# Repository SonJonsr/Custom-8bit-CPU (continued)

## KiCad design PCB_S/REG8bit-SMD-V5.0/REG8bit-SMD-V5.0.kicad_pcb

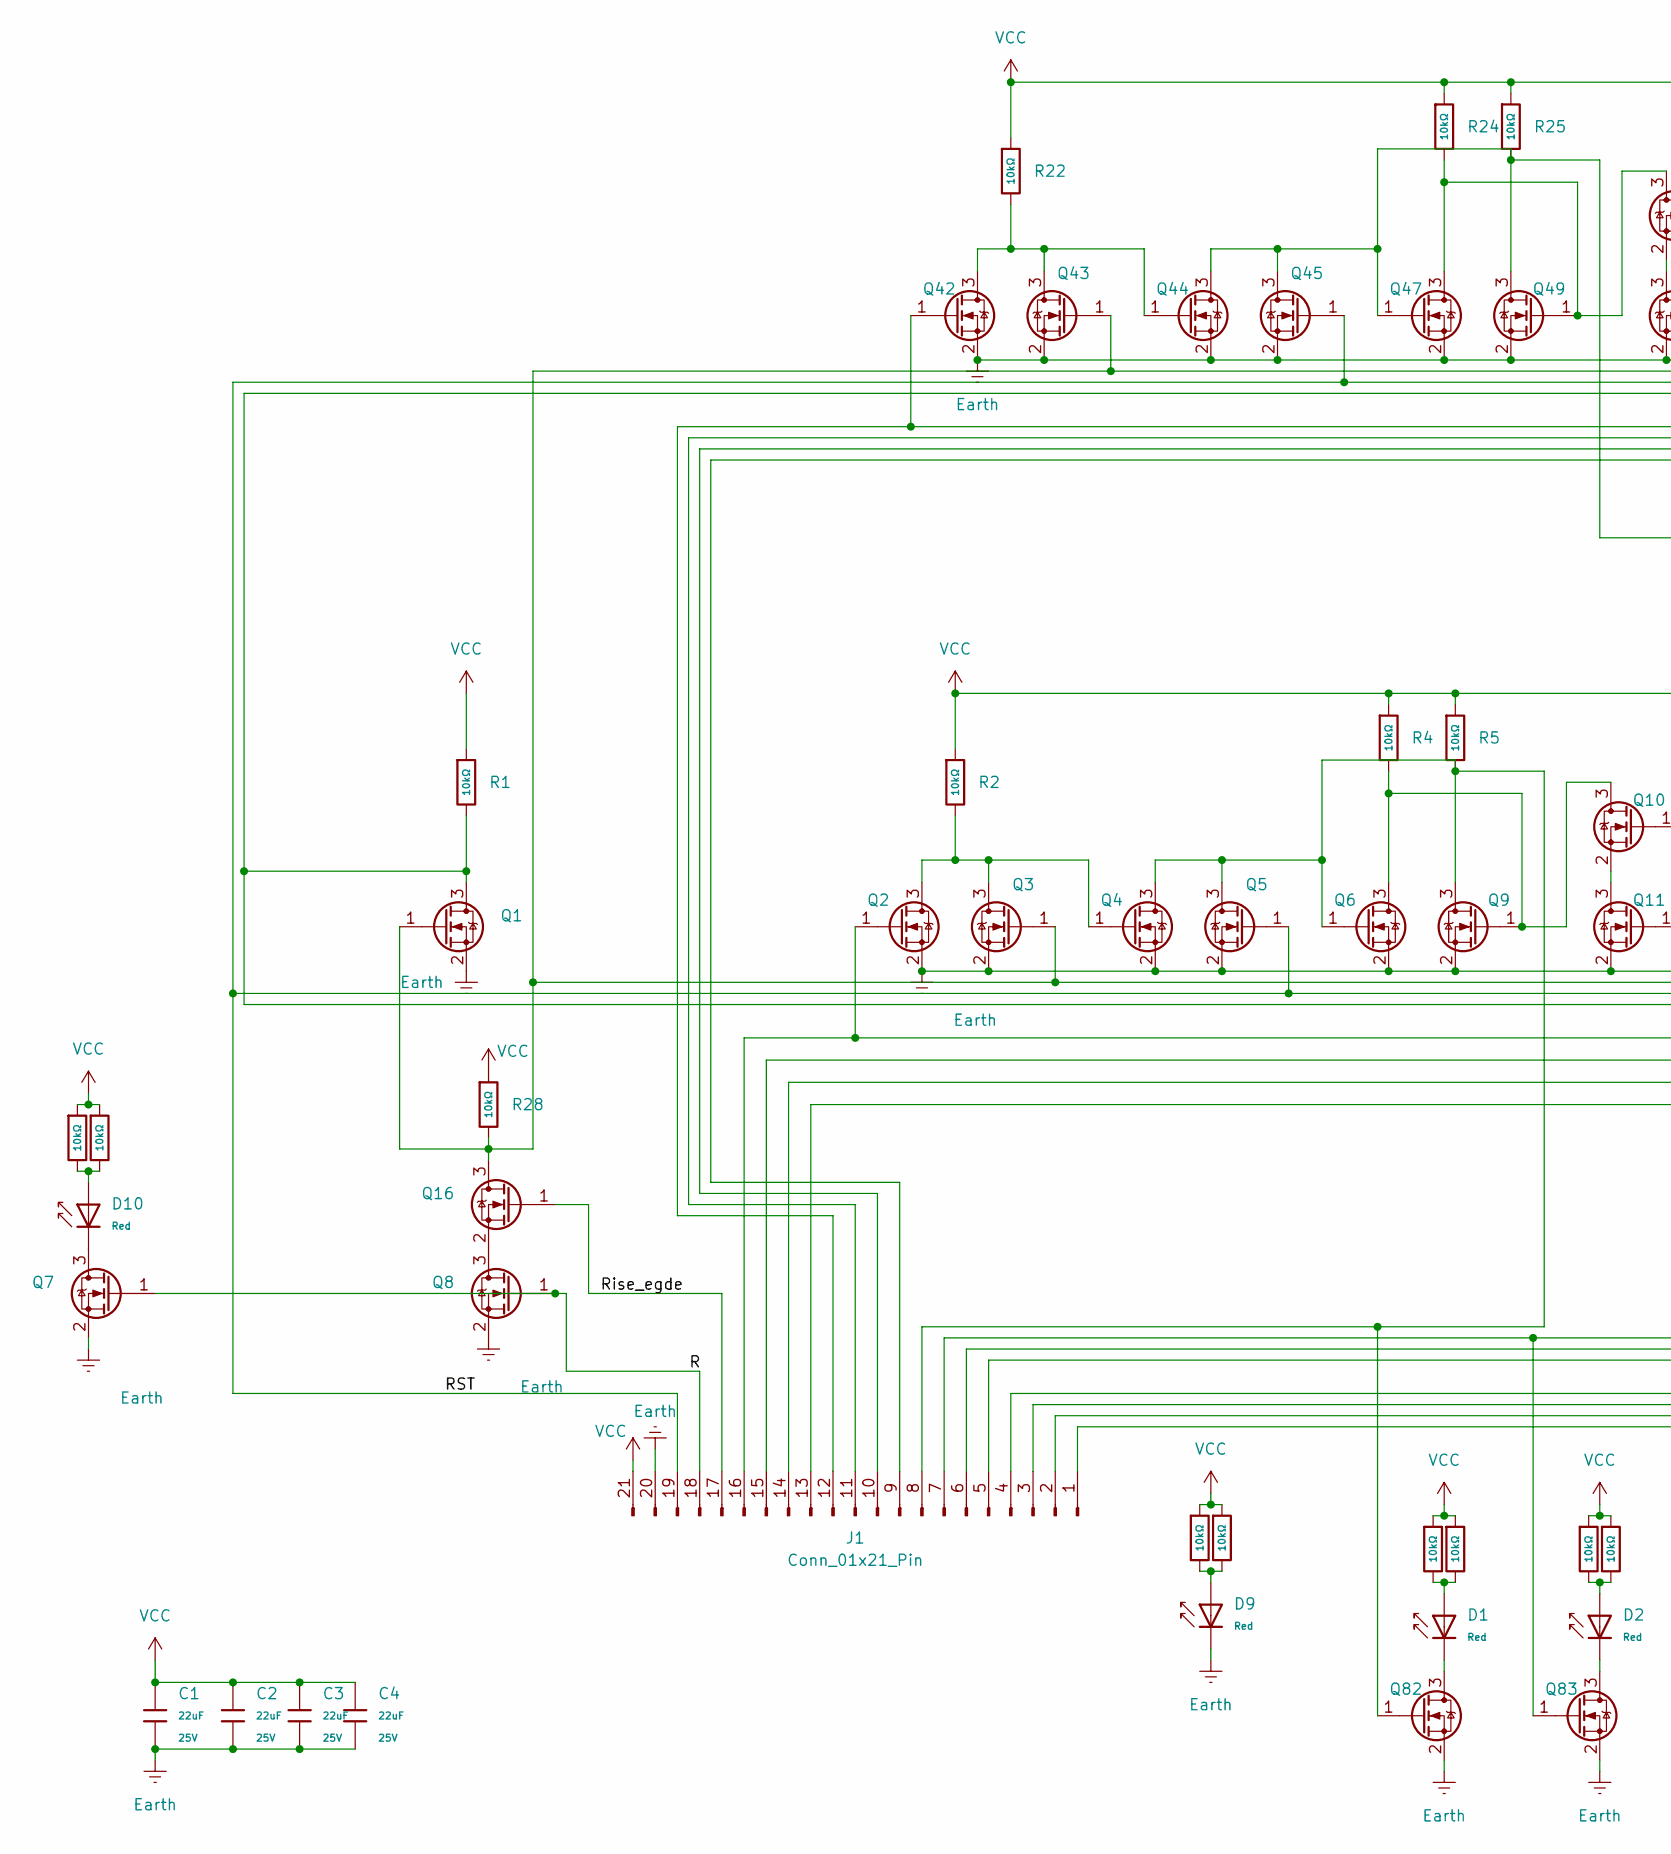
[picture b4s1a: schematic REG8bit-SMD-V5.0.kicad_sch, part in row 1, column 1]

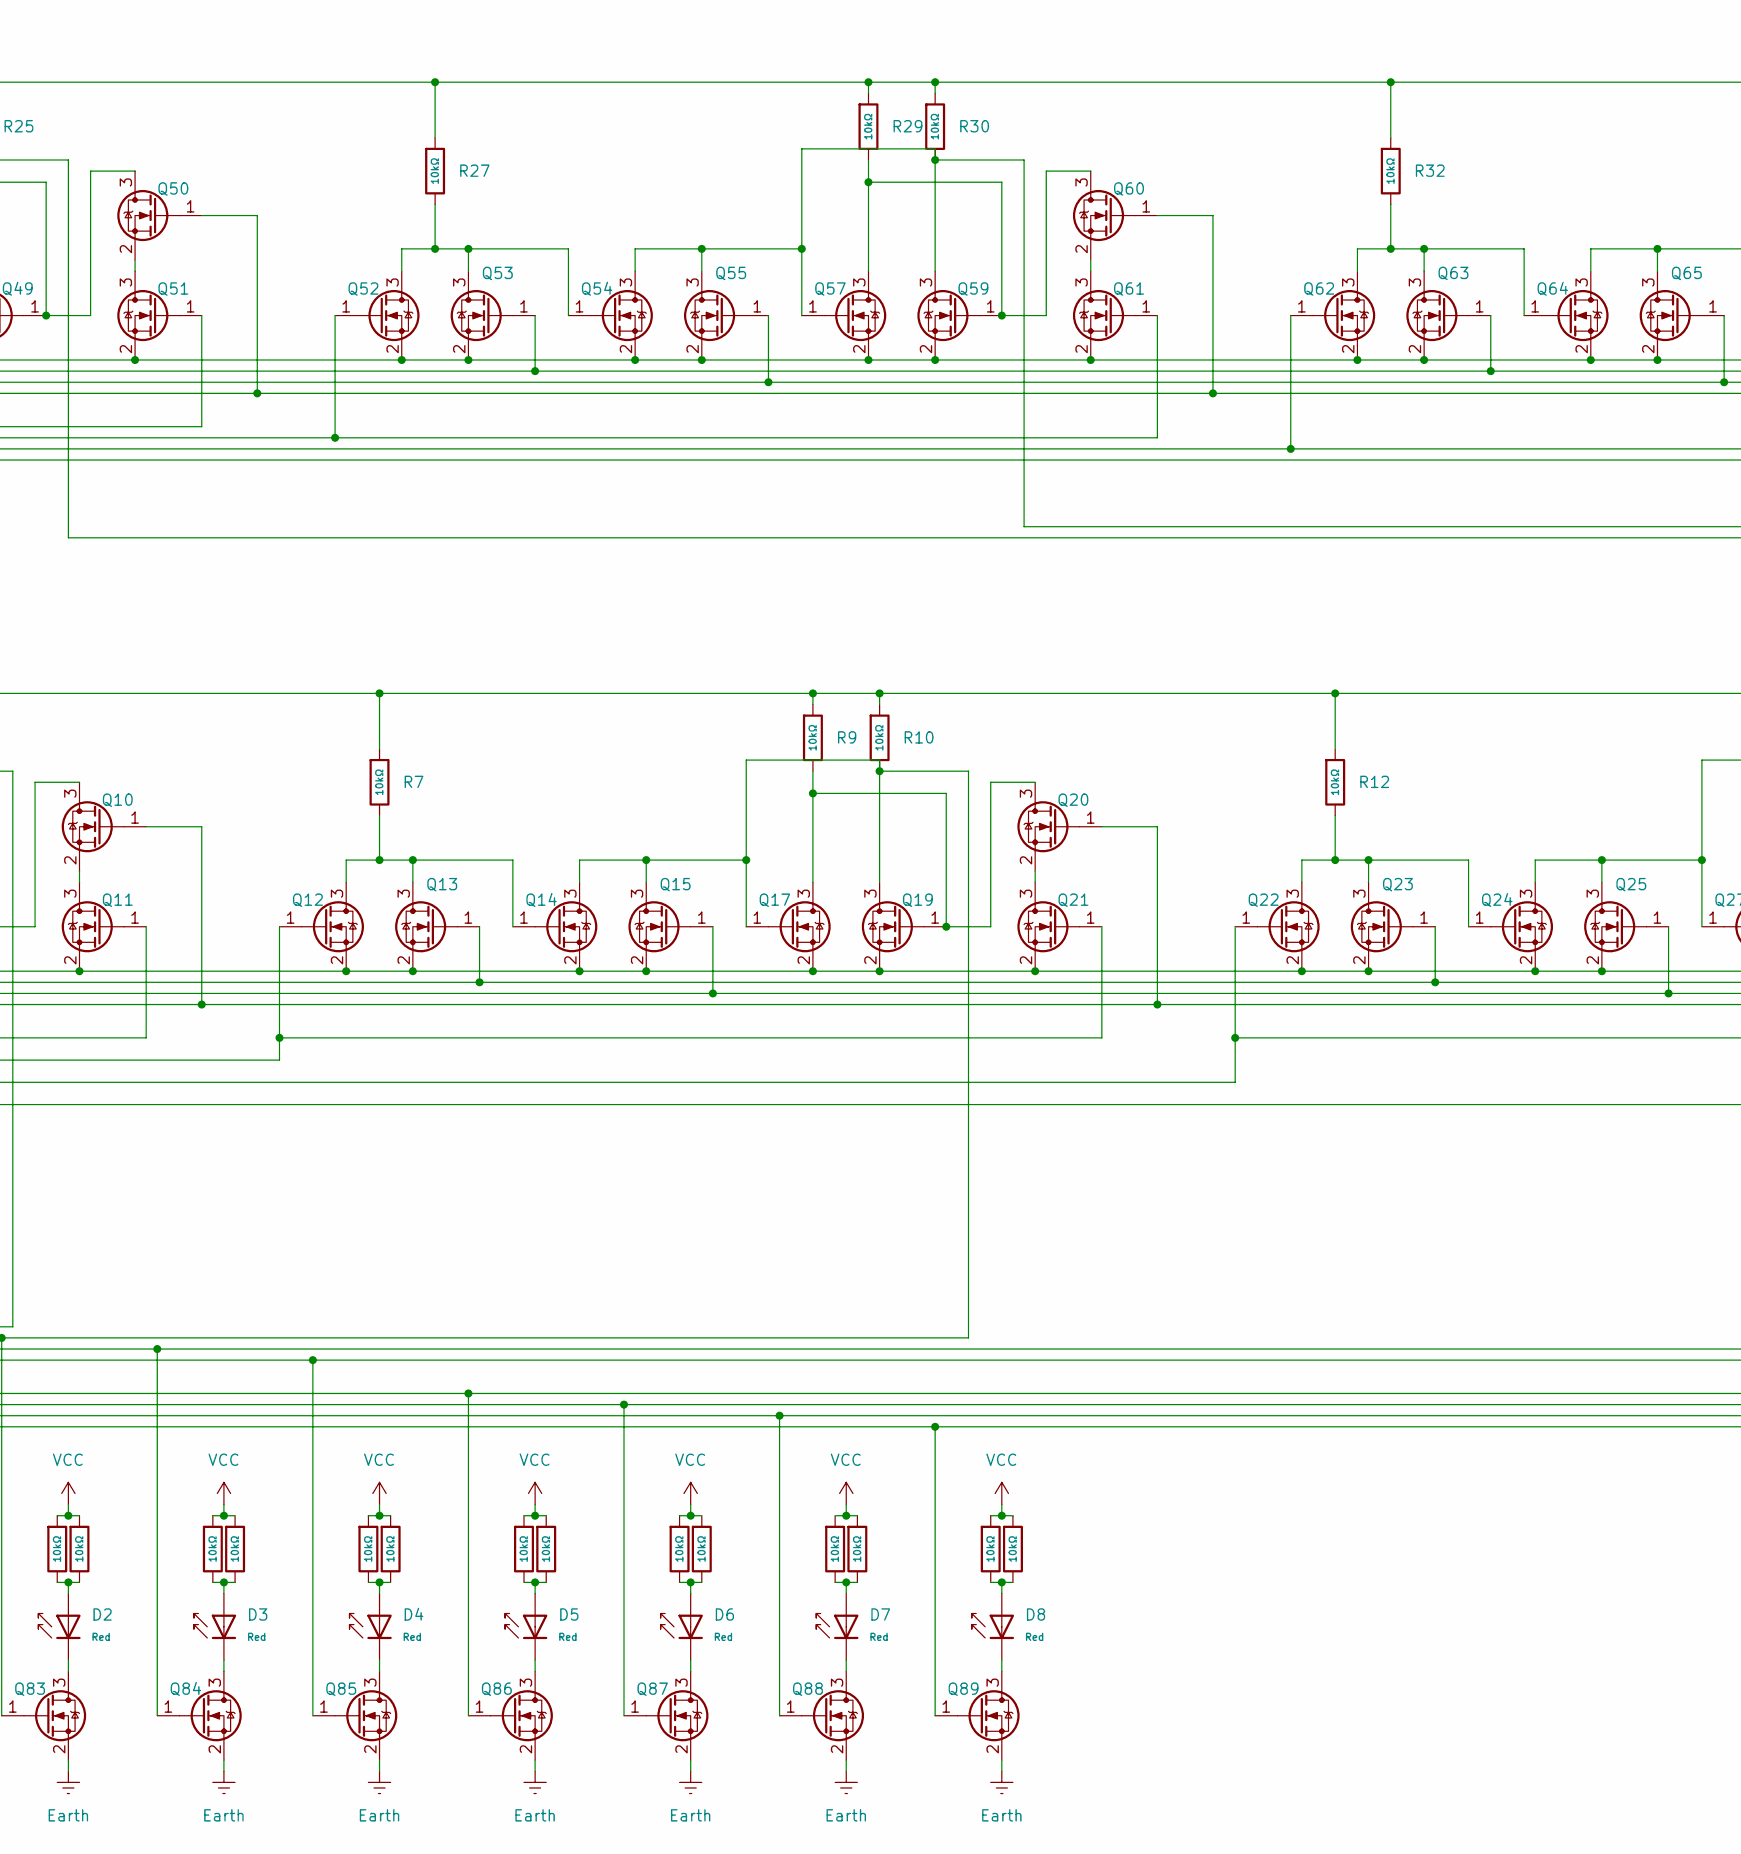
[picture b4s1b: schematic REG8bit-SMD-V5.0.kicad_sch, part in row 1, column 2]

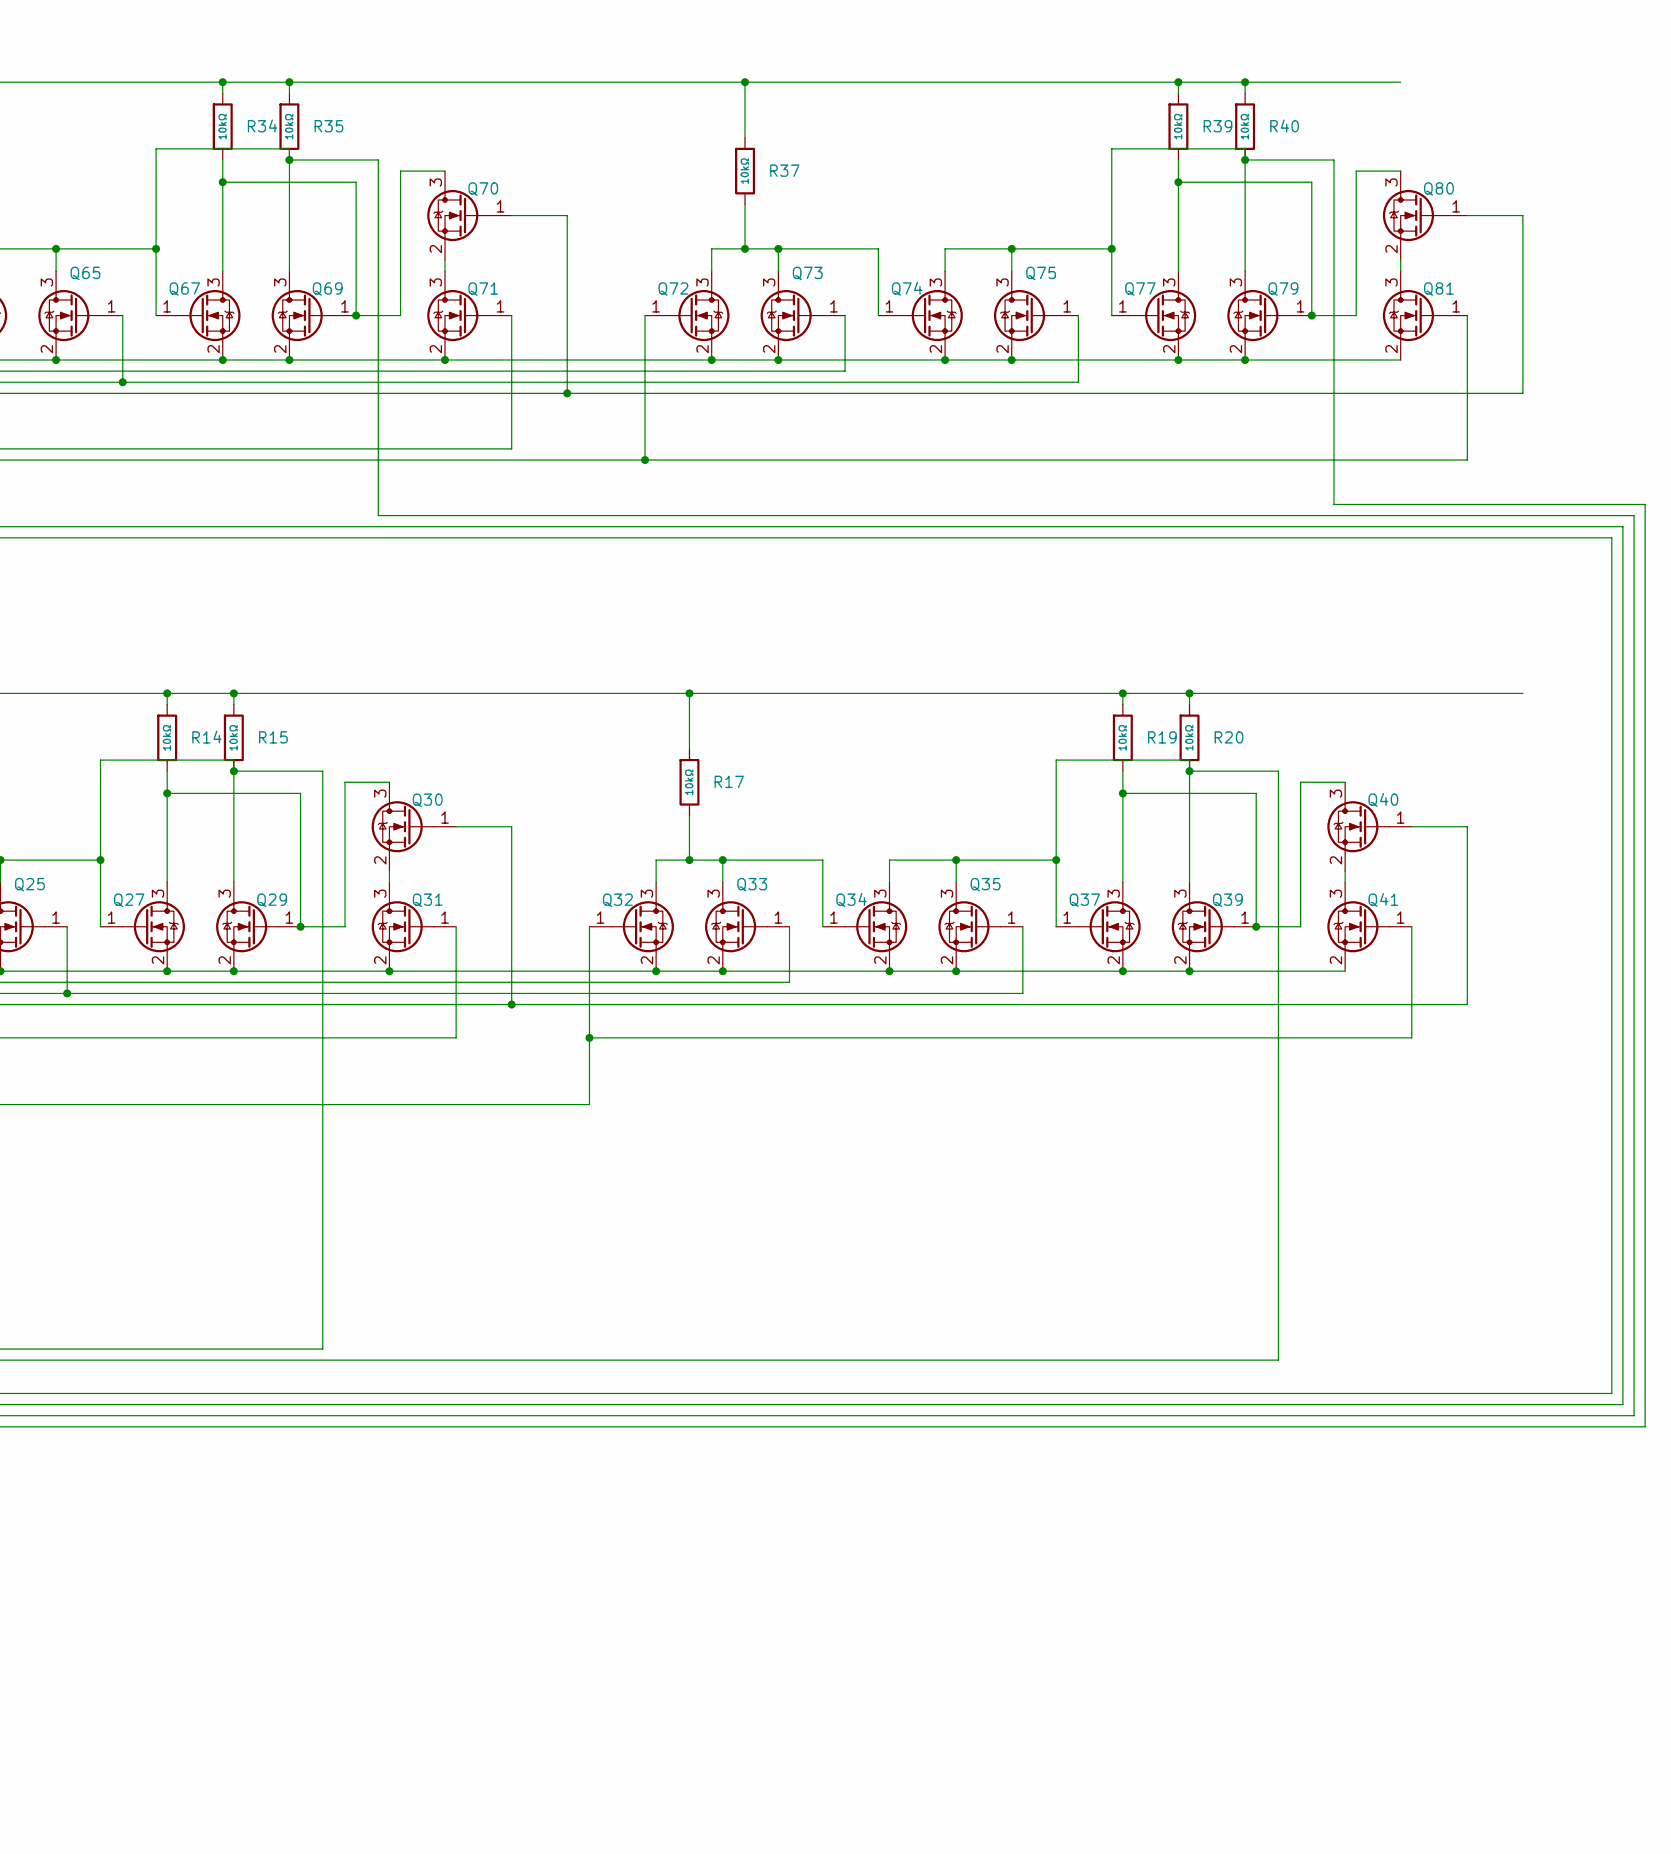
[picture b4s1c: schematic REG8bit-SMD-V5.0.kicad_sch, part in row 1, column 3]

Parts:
C1, C2, C3, C4: 22uF; C_0805; Voltage Rated 25V; Tolerance ±20%; Part CL21A226MAQNNNE; LCSC C45783
D1, D2, D3, D4, D5, D6, D7, D8, D9, D10: Red; D_0603; Part KT-0603R; LCSC C2286
J1: Conn_01x21_Pin; PinHeader_1x21_P2.54mm_Horizontal
Q1, Q2, Q3, Q4, Q5, Q6, Q7, Q8, Q9, Q10, Q11, Q12, Q13, Q14, Q15, Q16, Q17, Q19, Q20, Q21, Q22, Q23, Q24, Q25, Q27, Q29, Q30, Q31, Q32, Q33, Q34, Q35, Q37, Q39, Q40, Q41, Q42, Q43, Q44, Q45, Q47, Q49, Q50, Q51, Q52, Q53, Q54, Q55, Q57, Q59, Q60, Q61, Q62, Q63, Q64, Q65, Q67, Q69, Q70, Q71, Q72, Q73, Q74, Q75, Q77, Q79, Q80, Q81, Q82, Q83, Q84, Q85, Q86, Q87, Q88, Q89: 2N7002; SOT-23
R1, R2, R3, R4, R5, R6, R7, R8, R9, R10, R11, R12, R13, R14, R15, R16, R17, R18, R19, R20, R21, R22, R23, R24, R25, R26, R27, R28, R29, R30, R31, R32, R33, R34, R35, R36, R37, R38, R39, R40, R41, R42, R43, R44, R45, R46: 10kΩ; R_0402; Overload Voltage (Max) 50V; Tolerance ±1%; Part 0402WGF2002TCE; LCSC C25765

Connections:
/R: J1.18, Q7.1 (G), Q8.1 (G)
/RST: J1.19, Q5.1 (G), Q15.1 (G), Q25.1 (G), Q35.1 (G), Q45.1 (G), Q55.1 (G), Q65.1 (G), Q75.1 (G)
/Rise_egde: J1.17, Q16.1 (G)
Earth: C1.2, C2.2, C3.2, C4.2, D9.1, J1.20, Q1.2 (S), Q2.2 (S), Q3.2 (S), Q4.2 (S), Q5.2 (S), Q6.2 (S), Q7.2 (S), Q8.2 (S), Q9.2 (S), Q11.2 (S), Q12.2 (S), Q13.2 (S), Q14.2 (S), Q15.2 (S), Q17.2 (S), Q19.2 (S), Q21.2 (S), Q22.2 (S), Q23.2 (S), Q24.2 (S), Q25.2 (S), Q27.2 (S), Q29.2 (S), Q31.2 (S), Q32.2 (S), Q33.2 (S), Q34.2 (S), Q35.2 (S), Q37.2 (S), Q39.2 (S), Q41.2 (S), Q42.2 (S), Q43.2 (S), Q44.2 (S), Q45.2 (S), Q47.2 (S), Q49.2 (S), Q51.2 (S), Q52.2 (S), Q53.2 (S), Q54.2 (S), Q55.2 (S), Q57.2 (S), Q59.2 (S), Q61.2 (S), Q62.2 (S), Q63.2 (S), Q64.2 (S), Q65.2 (S), Q67.2 (S), Q69.2 (S), Q71.2 (S), Q72.2 (S), Q73.2 (S), Q74.2 (S), Q75.2 (S), Q77.2 (S), Q79.2 (S), Q81.2 (S), Q82.2 (S), Q83.2 (S), Q84.2 (S), Q85.2 (S), Q86.2 (S), Q87.2 (S), Q88.2 (S), Q89.2 (S)
unnamed: D1.2, R8.2, R11.2
unnamed: D2.2, R13.2, R16.2
unnamed: D3.2, R18.2, R21.2
unnamed: D4.2, R23.2, R31.2
unnamed: D5.2, R33.2, R36.2
unnamed: D6.2, R38.2, R41.2
unnamed: D7.2, R42.2, R43.2
unnamed: D8.2, R44.2, R45.2
unnamed: D9.2, R3.2, R6.2
unnamed: D10.2, R26.2, R46.2
unnamed: J1.1, Q74.3 (D), Q75.3 (D), Q77.1 (G), Q79.3 (D), Q89.1 (G), R40.2
unnamed: J1.2, Q64.3 (D), Q65.3 (D), Q67.1 (G), Q69.3 (D), Q88.1 (G), R35.2
unnamed: J1.3, Q54.3 (D), Q55.3 (D), Q57.1 (G), Q59.3 (D), Q87.1 (G), R30.2
unnamed: J1.4, Q44.3 (D), Q45.3 (D), Q47.1 (G), Q49.3 (D), Q86.1 (G), R25.2
unnamed: J1.5, Q34.3 (D), Q35.3 (D), Q37.1 (G), Q39.3 (D), Q85.1 (G), R20.2
unnamed: J1.6, Q24.3 (D), Q25.3 (D), Q27.1 (G), Q29.3 (D), Q84.1 (G), R15.2
unnamed: J1.7, Q14.3 (D), Q15.3 (D), Q17.1 (G), Q19.3 (D), Q83.1 (G), R10.2
unnamed: J1.8, Q4.3 (D), Q5.3 (D), Q6.1 (G), Q9.3 (D), Q82.1 (G), R5.2
unnamed: J1.9, Q72.1 (G), Q81.1 (G)
unnamed: J1.10, Q62.1 (G), Q71.1 (G)
unnamed: J1.11, Q52.1 (G), Q61.1 (G)
unnamed: J1.12, Q42.1 (G), Q51.1 (G)
unnamed: J1.13, Q32.1 (G), Q41.1 (G)
unnamed: J1.14, Q22.1 (G), Q31.1 (G)
unnamed: J1.15, Q12.1 (G), Q21.1 (G)
unnamed: J1.16, Q2.1 (G), Q11.1 (G)
unnamed: Q1.3 (D), Q10.1 (G), Q20.1 (G), Q30.1 (G), Q40.1 (G), Q50.1 (G), Q60.1 (G), Q70.1 (G), Q80.1 (G), R1.2
unnamed: Q1.1 (G), Q3.1 (G), Q13.1 (G), Q16.3 (D), Q23.1 (G), Q33.1 (G), Q43.1 (G), Q53.1 (G), Q63.1 (G), Q73.1 (G), R28.2
unnamed: Q2.3 (D), Q3.3 (D), Q4.1 (G), R2.2
unnamed: D10.1, Q7.3 (D)
unnamed: Q6.3 (D), Q9.1 (G), Q10.3 (D), R4.2
unnamed: Q10.2 (S), Q11.3 (D)
unnamed: Q12.3 (D), Q13.3 (D), Q14.1 (G), R7.2
unnamed: Q8.3 (D), Q16.2 (S)
unnamed: Q17.3 (D), Q19.1 (G), Q20.3 (D), R9.2
unnamed: Q20.2 (S), Q21.3 (D)
unnamed: Q22.3 (D), Q23.3 (D), Q24.1 (G), R12.2
unnamed: Q27.3 (D), Q29.1 (G), Q30.3 (D), R14.2
unnamed: Q30.2 (S), Q31.3 (D)
unnamed: Q32.3 (D), Q33.3 (D), Q34.1 (G), R17.2
unnamed: Q37.3 (D), Q39.1 (G), Q40.3 (D), R19.2
unnamed: Q40.2 (S), Q41.3 (D)
unnamed: Q42.3 (D), Q43.3 (D), Q44.1 (G), R22.2
unnamed: Q47.3 (D), Q49.1 (G), Q50.3 (D), R24.2
unnamed: Q50.2 (S), Q51.3 (D)
unnamed: Q52.3 (D), Q53.3 (D), Q54.1 (G), R27.2
unnamed: Q57.3 (D), Q59.1 (G), Q60.3 (D), R29.2
unnamed: Q60.2 (S), Q61.3 (D)
unnamed: Q62.3 (D), Q63.3 (D), Q64.1 (G), R32.2
unnamed: Q67.3 (D), Q69.1 (G), Q70.3 (D), R34.2
unnamed: Q70.2 (S), Q71.3 (D)
unnamed: Q72.3 (D), Q73.3 (D), Q74.1 (G), R37.2
unnamed: Q77.3 (D), Q79.1 (G), Q80.3 (D), R39.2
unnamed: Q80.2 (S), Q81.3 (D)
unnamed: D1.1, Q82.3 (D)
unnamed: D2.1, Q83.3 (D)
unnamed: D3.1, Q84.3 (D)
unnamed: D4.1, Q85.3 (D)
unnamed: D5.1, Q86.3 (D)
unnamed: D6.1, Q87.3 (D)
unnamed: D7.1, Q88.3 (D)
unnamed: D8.1, Q89.3 (D)
VCC: C1.1, C2.1, C3.1, C4.1, J1.21, R1.1, R2.1, R3.1, R4.1, R5.1, R6.1, R7.1, R8.1, R9.1, R10.1, R11.1, R12.1, R13.1, R14.1, R15.1, R16.1, R17.1, R18.1, R19.1, R20.1, R21.1, R22.1, R23.1, R24.1, R25.1, R26.1, R27.1, R28.1, R29.1, R30.1, R31.1, R32.1, R33.1, R34.1, R35.1, R36.1, R37.1, R38.1, R39.1, R40.1, R41.1, R42.1, R43.1, R44.1, R45.1, R46.1

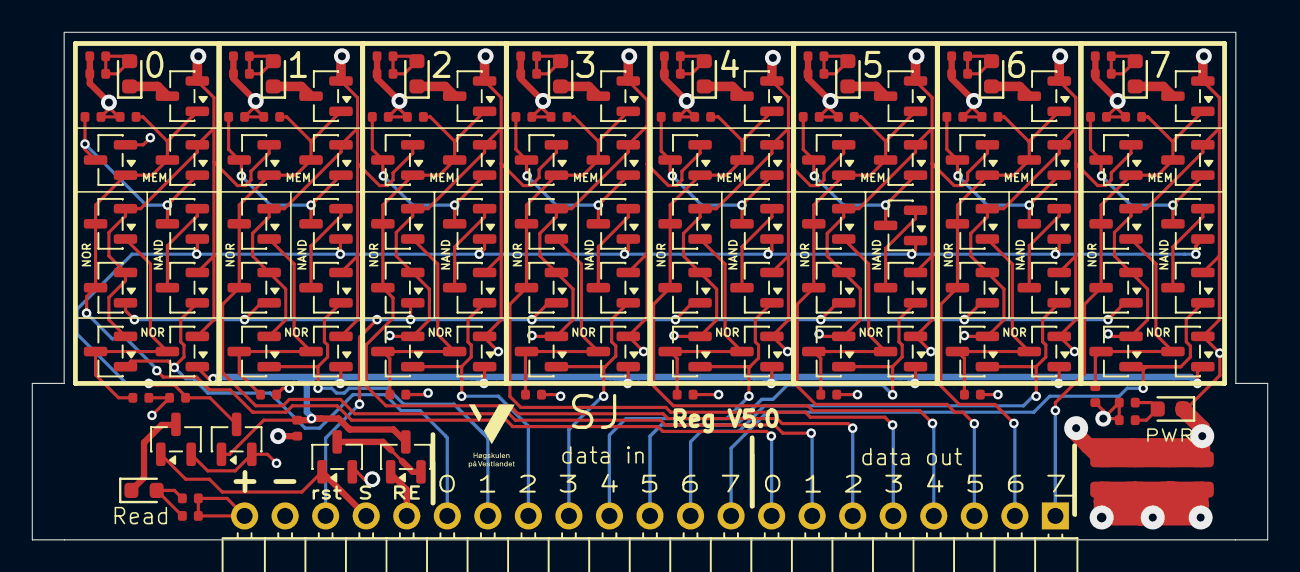
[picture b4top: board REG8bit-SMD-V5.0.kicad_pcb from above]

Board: 4 copper layers, 77.4 x 31.8 mm, 137 parts (0 on the bottom side), 67 nets.

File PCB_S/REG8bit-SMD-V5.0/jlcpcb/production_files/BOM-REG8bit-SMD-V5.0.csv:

Comment,Designator,Footprint,LCSC,Quantity
10kΩ,"R1,R10,R11,R12,R13,R14,R15,R16,R17,R18,R19,R2,R20,R21,R22,R23,R24,R25,R26,R27,R28,R29,R3,R30,R31,R32,R33,R34,R35,R36,R37,R38,R39,R4,R40,R41,R42,R43,R44,R45,R46,R5,R6,R7,R8,R9",R_0402,C25744,46
22uF,"C1,C2,C3,C4",C_0805,C45783,4
2N7002,"Q1,Q10,Q11,Q12,Q13,Q14,Q15,Q16,Q17,Q19,Q2,Q20,Q21,Q22,Q23,Q24,Q25,Q27,Q29,Q3,Q30,Q31,Q32,Q33,Q34,Q35,Q37,Q39,Q4,Q40,Q41,Q42,Q43,Q44,Q45,Q47,Q49,Q5,Q50,Q51,Q52,Q53,Q54,Q55,Q57,Q59,Q6,Q60,Q61,Q62,Q63,Q64,Q65,Q67,Q69,Q7,Q70,Q71,Q72,Q73,Q74,Q75,Q77,Q79,Q8,Q80,Q81,Q82,Q83,Q84,Q85,Q86,Q87,Q88,Q89,Q9",SOT-23,C8545,76
Red,"D1,D10,D2,D3,D4,D5,D6,D7,D8,D9",D_0603,C2286,10
Conn_01x21_Pin,J1,PinHeader_1x21_P2.54mm_Horizontal,,1

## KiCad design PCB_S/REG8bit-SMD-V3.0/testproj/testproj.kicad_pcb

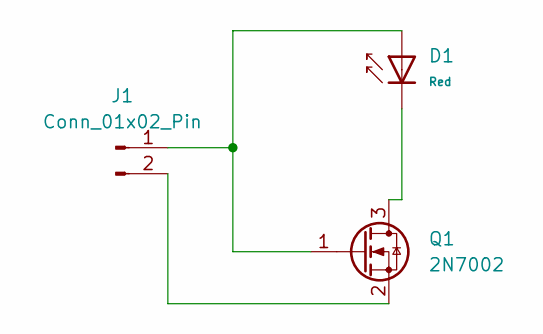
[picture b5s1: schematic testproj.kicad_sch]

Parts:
D1: Red; D_0805; Forward Voltage (VF) 1.6V~2.6V; Part NCD0805R1; LCSC C84256
J1: Conn_01x02_Pin; AMASS_XT30PW-F_1x02_P2.50mm_Horizontal
Q1: 2N7002; SOT-23

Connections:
unnamed: D1.2, J1.1, Q1.1 (G)
unnamed: J1.2, Q1.2 (S)
unnamed: D1.1, Q1.3 (D)

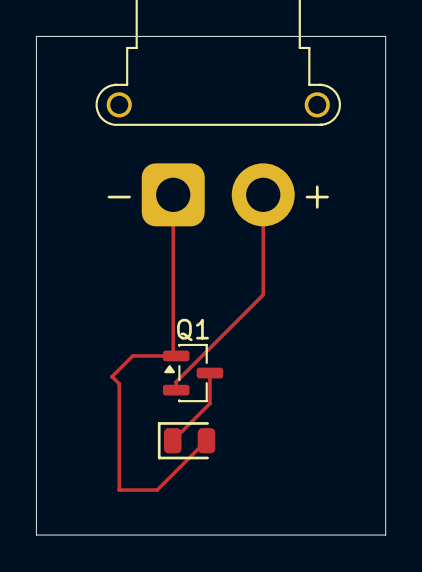
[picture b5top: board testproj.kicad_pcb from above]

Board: 2 copper layers, 19.4 x 27.7 mm, 3 parts (0 on the bottom side), 3 nets.

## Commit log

2026-01-20 Added FPGA CPU
2026-01-20 Adding compiler files
2026-01-20 Making visual studio work
    Fixing the file systems in visual studio
2026-01-20 Files fixed
2026-01-20 Warnings and errors detection
2026-01-21 A lot of fixes to the compiler
    Made a C text splitter that splits up key charecters like + or - and makes spaces in front and behind. example varX=varY+varZ will become varX = varY + varZ. Simplifying the reading process. And impl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
2026-01-21 --II--
2026-01-23 CPU works fine now
    changed the fpga CPU
2026-01-25 Starting on the creation of the ALU
2026-01-25 testing github for KICAD
2026-01-25 Making CPU_V2
2026-01-25 ALU_pcb
2026-01-25 Making the FPGA CPU V2
2026-01-25 FPGA_CPU_V2 no errors
2026-01-25 Fixed new opcodes
2026-01-28 added registers 8 bit
2026-01-29 Litt fpga rot
2026-01-30 Legger til forstudie filen så vi kan lettere jobbe med den senere.
2026-01-30 Gantt mal lagt til
2026-02-03 Legger til Hoved-Gantt-diagram
2026-02-04 pcb making
2026-02-05 New Register half done
2026-02-05 PCB : REG8bit v4 done
2026-02-05 sim
    Tried the spice sim : the sim did not work at all
2026-02-06 REG8bit-v4.1
2026-02-06 8-Bit register is done
2026-02-12 sendt the reg8bit
2026-02-17 ALU_V1.0 schematic done
2026-02-18 ALU_V1.0
    Creating the ALU PCB
2026-02-18 ALU_V1.0 WIP
    PCB size doesnt matter??
2026-02-20 ALU_V1.0 WIP
    making pcb
2026-02-21 ALU V1.0 done?
2026-02-21 ALU V1.0 more done
2026-02-24 ALU_V1.0_Done
2026-02-24 ALU_V1.0 silk
2026-02-25 Reg holder v1.0 start
2026-02-25 ALU d
2026-02-26 REG holder V1.0
2026-02-26 ssss
2026-02-26 REG_HOLDER_V1.0 done
2026-03-02 Updated all boards
    change the resistor for all the LEDs and used the 2x8 connector
2026-03-05 Testing things
2026-03-10 Cpu controller unit start
2026-03-17 Controller V1.0 work
2026-03-19 small
2026-03-19 controll uint work
2026-03-20 Controller unit v1.0 wip
2026-03-22 cercuit done controller unit v1.0 ?
2026-03-23 Controller unit PCB wip
2026-03-27 CONTROLLER UNIT V1.0 done?
    JCL : exceed 2048 error
2026-03-27 CONTROLLER unit v1.0 without a jlc issue
    Switch BOM file to BOM_T2.csv
2026-03-28 FPGA modules: PS2, VGA, PS2_VGA_MEMORY_TESTBENCH. Snake written in C as close to our compiler C as possible
2026-03-28 Remove temporary test file
2026-03-28 Controller unit v1.0 done & Level Shifter fpga v1.0 done
2026-03-29 Started the huge chungus wide combined cpu
2026-03-29 almost done
2026-03-29 Snake is now more optimized for the 16-bit addressing that the arrays utilize.
2026-03-30 order tomorrow
2026-03-31 Finaly sent the last pcbs
2026-04-13 Backup before DAT102 obligatory test.
2026-04-21 motherboard version 1 and snake game adjusted for screen with 64 ascii width
2026-04-23 Updated some memory stuff
2026-04-24 rotary encoder
2026-04-24 haaa
2026-04-26 Add clock controller updates and KiCad project files
2026-04-28 compiler functunalities
2026-04-28 If statments good for 8bit tests (==, !=, <, >)
2026-04-29 MEM[x] = a;
2026-04-29 compiler functionalities are done
2026-04-30 test.c is a "hello world!" test
2026-04-30 commit before merge
2026-04-30 hello test
2026-04-30 faaaan
2026-04-30 Changed CLOCK_25 to just a signal half as fast as CLOCK_50. This fixed the screen not turning on for some reason?
2026-05-02 Here
2026-05-03 if and while for 16 bit now out
2026-05-03 motherboard_ver_2! Now with clock_controller_ver_2 and physical rst_n and clk_slow buttonsgit add .! ALSO ROTARY ENCODER MAKES A DEBUT
2026-05-03 AND, OR, XOR is in now
2026-05-04 Faaaak Jacob
2026-05-04 snake
2026-05-04 fix 16 = 16 - 16
2026-05-04 length counter
2026-05-04 snake shit again, this is a commit before a linux update
2026-05-08 All the code for all snake versions 3.4 to 4.6. Version 3.21 complete snake without score, and version 4.6 complete snake with score and high score (RECOMMENDED VERSION). Also some minor FPGA adjustm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
2026-05-09 git satt opp for latex skriving
2026-05-09 lmao
2026-05-09 updating gitignore for latex setup
2026-05-09 jacob er dårlig på å skrive:c
2026-05-10 dårlig skrevet P(i)S(s)/2-modul tekst
2026-05-16 hjelp meg gud
2026-05-18 AAAAAAAAAAAAAAAAAAHHHHHHHHHHHH
2026-05-19 Fikk skrevet en del i går B)
2026-06-24 lmao mye fpga
2026-06-25 LMAO LMAO LMAO LMFAO
